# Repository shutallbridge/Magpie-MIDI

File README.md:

# Magpie-MIDI

For more information about this project, please visit the link:
https://hackaday.io/project/174136-magpie-midi-an-adaptive-midiinterface-harmonica

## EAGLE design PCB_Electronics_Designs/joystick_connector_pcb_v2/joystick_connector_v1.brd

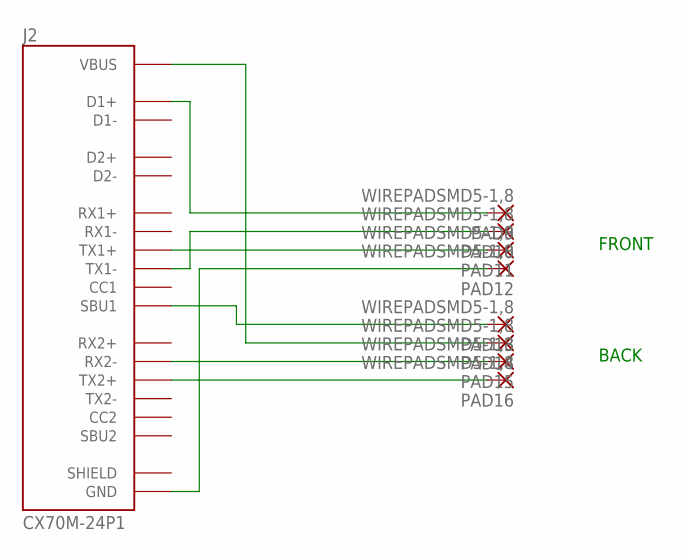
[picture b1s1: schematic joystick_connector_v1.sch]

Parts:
J2: CX70M-24P1; HRS_CX70M-24P1
PAD9, PAD10, PAD11, PAD12, PAD13, PAD14, PAD15, PAD16: WIREPADSMD5-1,8; 5-1,8

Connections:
unnamed: J2.A6 (D1+), PAD9.1
unnamed: J2.A3 (TX1-), PAD10.1
unnamed: J2.A2 (TX1+), PAD11.1
unnamed: J2.A1 (GND), J2.A12 (GND), J2.B1 (GND), J2.B12 (GND), PAD12.1
unnamed: J2.A8 (SBU1), PAD13.1
unnamed: J2.A4 (VBUS), J2.A9 (VBUS), J2.B4 (VBUS), J2.B9 (VBUS), PAD14.1
unnamed: J2.A10 (RX2-), PAD15.1
unnamed: J2.B2 (TX2+), PAD16.1
SHIELD: J2.S1 (SHIELD), J2.S2 (SHIELD), J2.S3 (SHIELD), J2.S4 (SHIELD), J2.S5 (SHIELD), J2.S5.1 (SHIELD), J2.S6 (SHIELD), J2.S6.1 (SHIELD)

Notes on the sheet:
FRONT
BACK

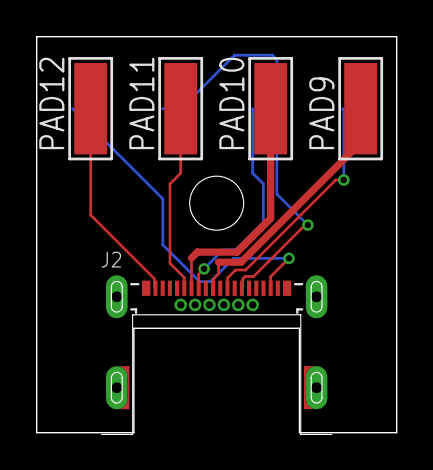
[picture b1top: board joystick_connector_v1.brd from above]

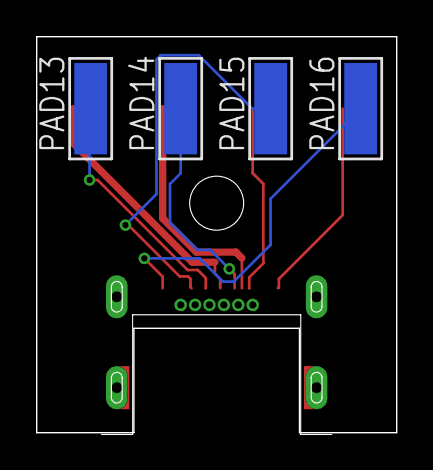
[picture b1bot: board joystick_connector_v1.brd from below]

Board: 2 copper layers, 20.0 x 22.1 mm, 9 parts (4 on the bottom side), 9 nets.

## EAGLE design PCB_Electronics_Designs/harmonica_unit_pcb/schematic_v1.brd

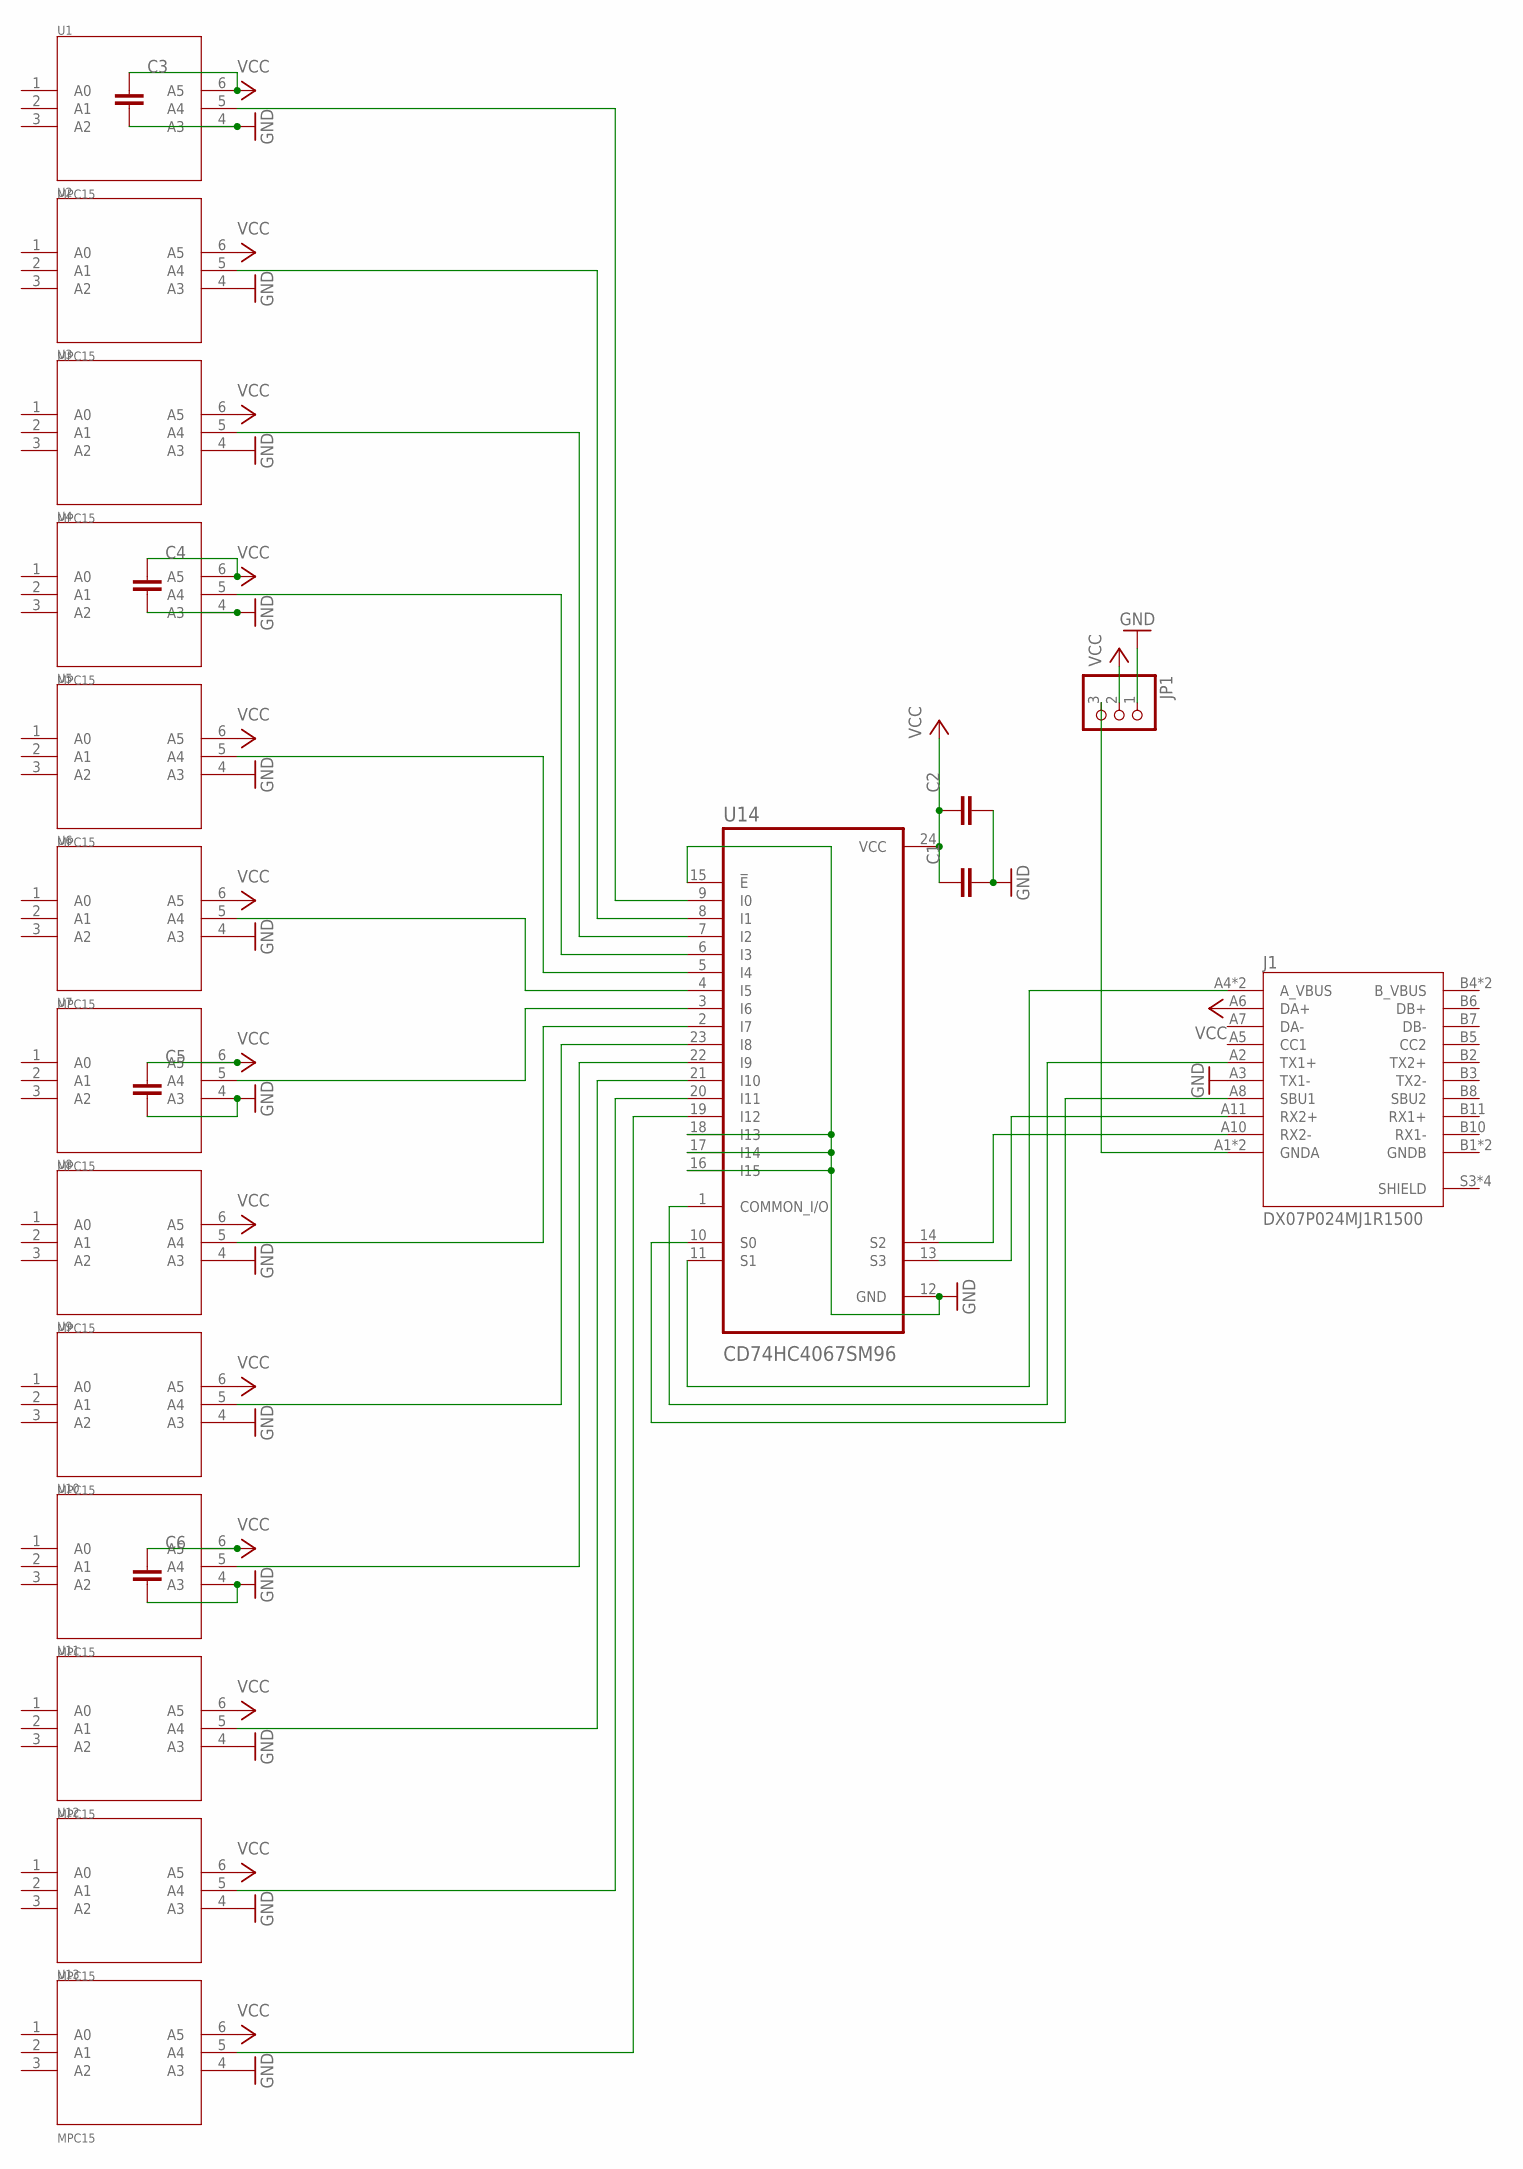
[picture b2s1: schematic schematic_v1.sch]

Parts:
C1, C2, C3, C4, C5, C6: C_CHIP-0805(2012-METRIC); CAPC2012X110
J1: DX07P024MJ1R1500; JAE_DX07P024MJ1R1500
JP1: PINHD-1X3/90; 1X03/90
U1, U2, U3, U4, U5, U6, U7, U8, U9, U10, U11, U12, U13: MPC15; DIP1000W53P254L850H340Q6B
U14: CD74HC4067SM96; SOP65P780X200-24N

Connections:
B_VBUS: J1.B4 (B_VBUS), J1.B9 (B_VBUS)
GND: C1.2, C2.2, C3.2, C4.2, C5.2, C6.2, J1.A3 (TX1-), JP1.1, U1.4 (A3), U2.4 (A3), U3.4 (A3), U4.4 (A3), U5.4 (A3), U6.4 (A3), U7.4 (A3), U8.4 (A3), U9.4 (A3), U10.4 (A3), U11.4 (A3), U12.4 (A3), U13.4 (A3), U14.12 (GND), U14.15 (!E), U14.16 (I15), U14.17 (I14), U14.18 (I13)
GNDB: J1.B1 (GNDB), J1.B12 (GNDB)
unnamed: U1.5 (A4), U14.9 (I0)
unnamed: U2.5 (A4), U14.8 (I1)
unnamed: U3.5 (A4), U14.7 (I2)
unnamed: U4.5 (A4), U14.6 (I3)
unnamed: U5.5 (A4), U14.5 (I4)
unnamed: U6.5 (A4), U14.4 (I5)
unnamed: U7.5 (A4), U14.3 (I6)
unnamed: U8.5 (A4), U14.2 (I7)
unnamed: U9.5 (A4), U14.23 (I8)
unnamed: U10.5 (A4), U14.22 (I9)
unnamed: U11.5 (A4), U14.21 (I10)
unnamed: U12.5 (A4), U14.20 (I11)
unnamed: U13.5 (A4), U14.19 (I12)
unnamed: J1.A4 (A_VBUS), J1.A9 (A_VBUS), U14.11 (S1)
unnamed: J1.A2 (TX1+), U14.1 (COMMON_I/O)
unnamed: J1.A8 (SBU1), U14.10 (S0)
unnamed: J1.A11 (RX2+), U14.13 (S3)
unnamed: J1.A10 (RX2-), U14.14 (S2)
unnamed: J1.A1 (GNDA), J1.A12 (GNDA), JP1.3
SHIELD: J1.S3 (SHIELD), J1.S4 (SHIELD), J1.S5 (SHIELD), J1.S6 (SHIELD)
VCC: C1.1, C2.1, C3.1, C4.1, C5.1, C6.1, J1.A6 (DA+), JP1.2, U1.6 (A5), U2.6 (A5), U3.6 (A5), U4.6 (A5), U5.6 (A5), U6.6 (A5), U7.6 (A5), U8.6 (A5), U9.6 (A5), U10.6 (A5), U11.6 (A5), U12.6 (A5), U13.6 (A5), U14.24 (VCC)

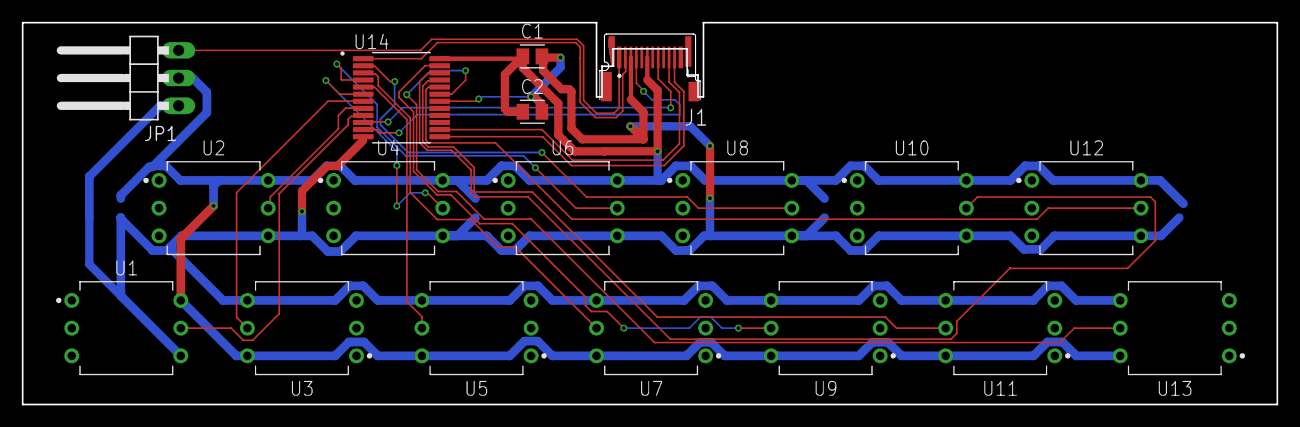
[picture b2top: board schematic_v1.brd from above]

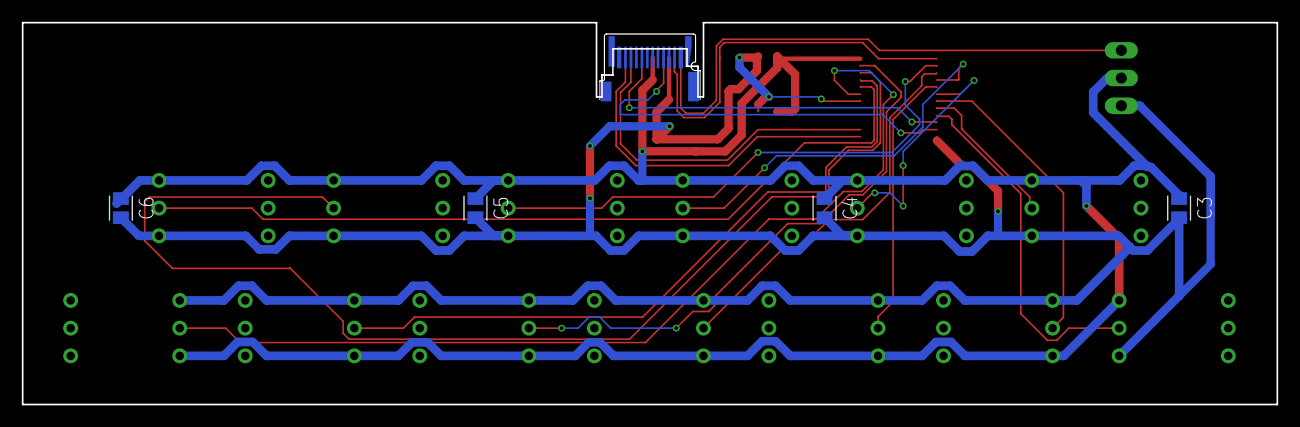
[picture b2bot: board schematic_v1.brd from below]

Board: 2 copper layers, 115.0 x 35.0 mm, 22 parts (4 on the bottom side), 24 nets.

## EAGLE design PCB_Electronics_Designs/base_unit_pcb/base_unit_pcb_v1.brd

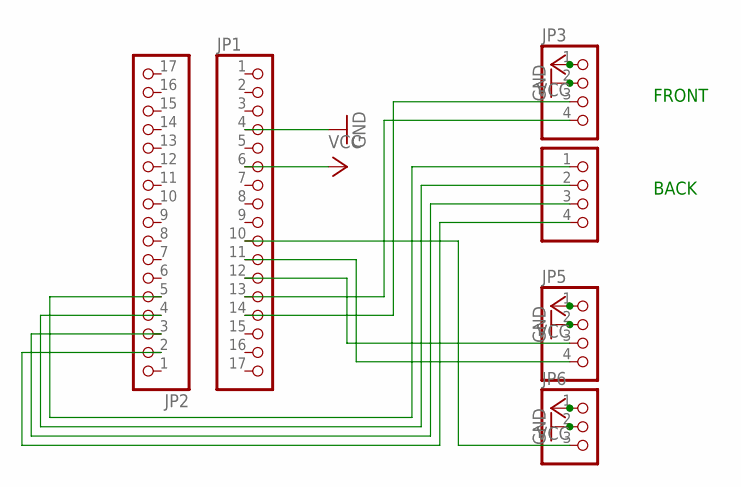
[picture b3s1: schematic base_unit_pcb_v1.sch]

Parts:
JP1, JP2: PINHD-1X17; 1X17
JP3, JP4, JP5: PINHD-1X4; 1X04
JP6: PINHD-1X3; 1X03

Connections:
GND: JP1.4, JP3.2, JP5.2, JP6.2
unnamed: JP1.12, JP5.3
unnamed: JP1.11, JP5.4
unnamed: JP1.14, JP3.3
unnamed: JP1.13, JP3.4
unnamed: JP2.5, JP4.1
unnamed: JP2.4, JP4.2
unnamed: JP2.3, JP4.3
unnamed: JP2.2, JP4.4
unnamed: JP1.10, JP6.3
VCC: JP1.6, JP3.1, JP5.1, JP6.1

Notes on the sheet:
FRONT
BACK

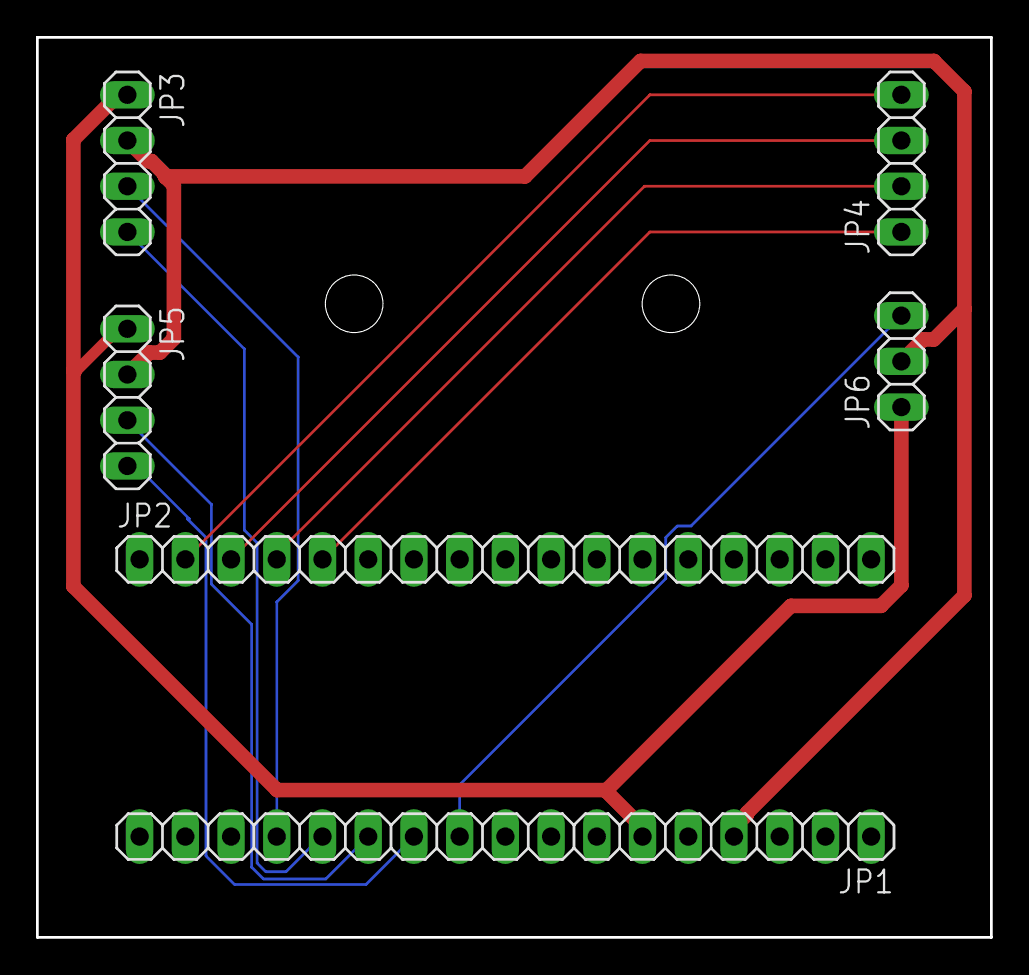
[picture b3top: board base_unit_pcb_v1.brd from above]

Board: 2 copper layers, 53.0 x 50.0 mm, 6 parts (0 on the bottom side), 11 nets.

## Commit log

2020-09-08 folder organization
2020-09-13 classes improvements
2020-09-13 module updates
2020-10-06 update BOM
2020-10-06 update 3d files
